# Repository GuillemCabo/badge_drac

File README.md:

# badge_drac
Current schematic has some issues discovered after the first run.
If you are interested to make your own let me know and I will give more priority.

PCB art and FP are fine.

Badges gifted at ORConf 2019 have limited functionality. Only capacitive touch sensors,
buzzer, RGB leds and push buttons were tested.

Code ideas:
Two player reaction time game with touch buttons and LEDs
Closet alarm with ambient light sensor and buzzer.
Coordination minigame, you have to push righ left in function of led color, maybe put some music in the buzzer as well...

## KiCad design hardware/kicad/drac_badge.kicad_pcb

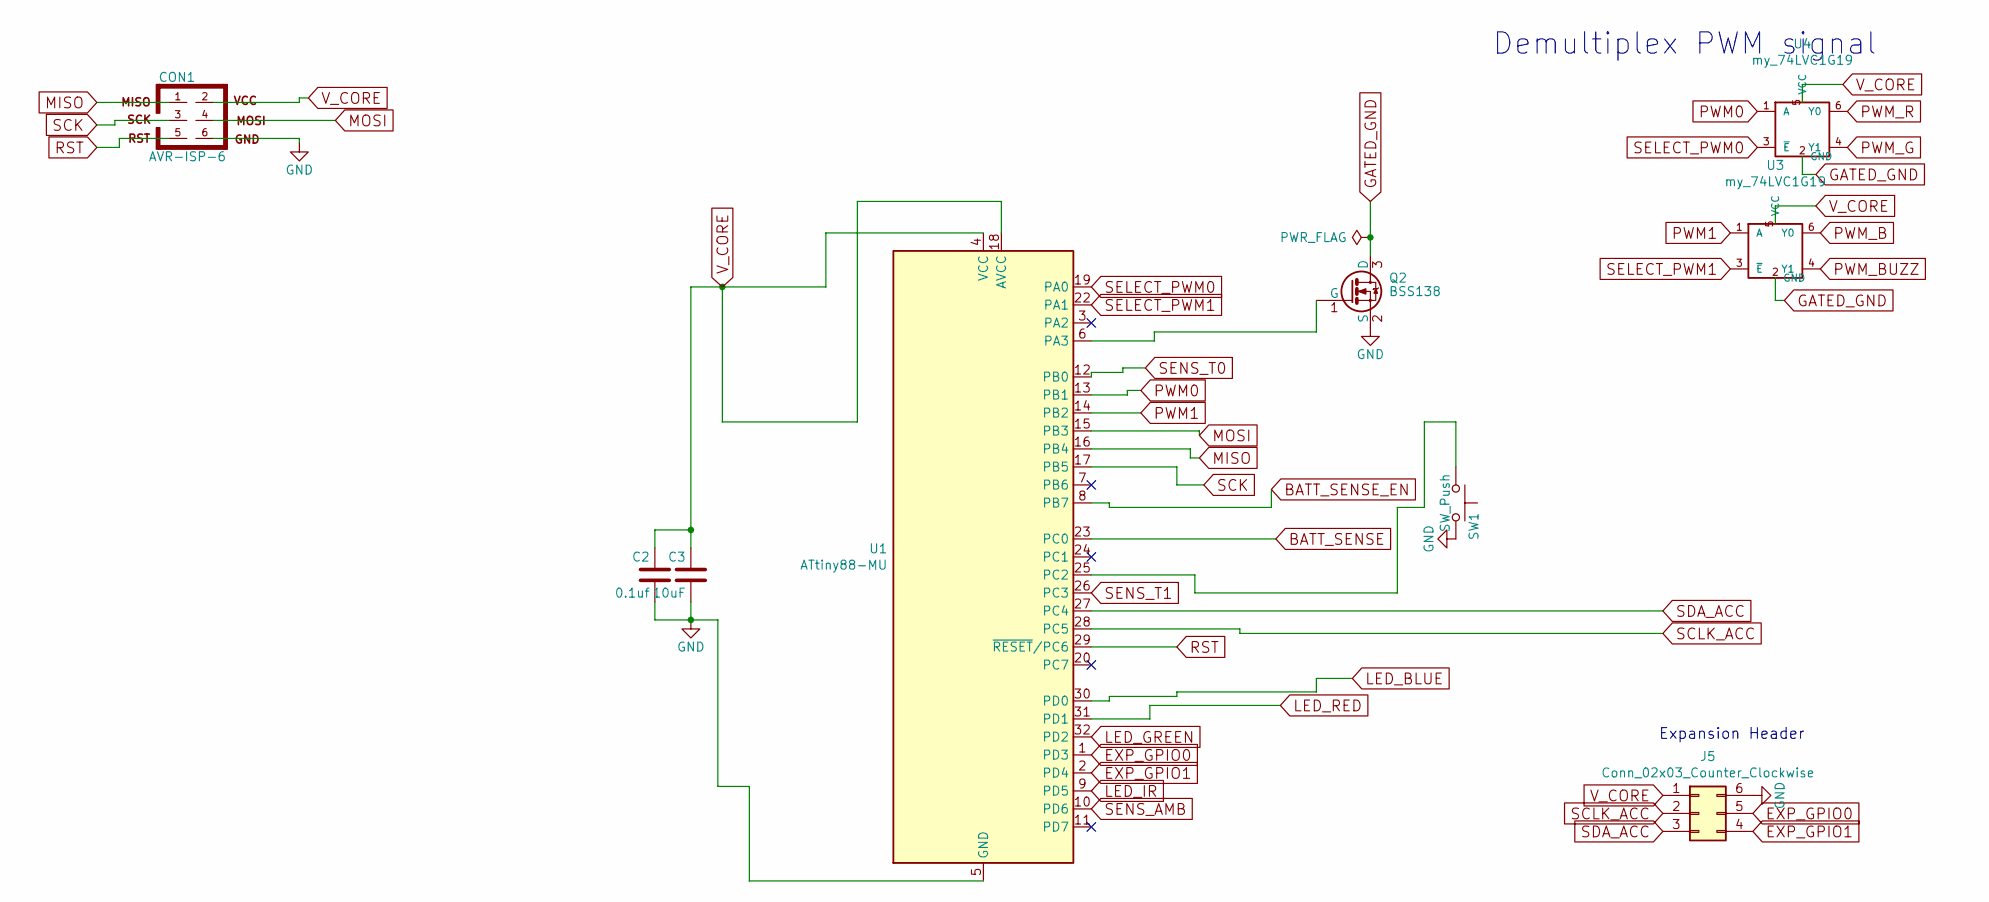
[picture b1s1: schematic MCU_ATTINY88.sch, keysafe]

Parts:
C2: 0.1uf; C_0603_1608Metric; MPN C0603C104J5RACTU; FARNELL # 2409037
C3: 10uF; C_0805_2012Metric; MPN C0805X106K9RACTU; FARNELL # 2776900
CON1: AVR-ISP-6; MERGED_TAGCONNECT_2.54mm; MPN NONE; FARNELL # NONE
J5: Conn_02x03_Counter_Clockwise; PinSocket_2x03_P2.54mm_Vertical_SMD
Q2: BSS138; SOT-23; MPN BSS138PW; FARNELL # 1907611
SW1: SW_Push; SW_Push_1P1T_NO_CK_KSC7xxJ; MPN EVQPUK02K; FARNELL # 2079467
U1: ATtiny88-MU; QFN-32-1EP_5x5mm_P0.5mm_EP3.1x3.1mm; MPN ATTINY88-MU; FARNELL # 1748549
U3, U4: my_74LVC1G19; SOT-363_SC-70-6

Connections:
BATT_SENSE: U1.23 (PC0); also elsewhere on the board
BATT_SENSE_EN: U1.8 (PB7); also elsewhere on the board
EXP_GPIO0: J5.5, U1.1 (PD3)
EXP_GPIO1: J5.4, U1.2 (PD4)
GATED_GND: Q2.3 (D), U3.2 (GND), U4.2 (GND); also elsewhere on the board
GND: C2.2, C3.2, CON1.6, J5.6, Q2.2 (S), SW1.2, U1.5 (GND), U1.21 (GND), U1.33 (GND); also elsewhere on the board
LED_BLUE: U1.30 (PD0); also elsewhere on the board
LED_GREEN: U1.32 (PD2); also elsewhere on the board
LED_IR: U1.9 (PD5); also elsewhere on the board
LED_RED: U1.31 (PD1); also elsewhere on the board
MISO: CON1.1, U1.16 (PB4)
MOSI: CON1.4, U1.15 (PB3)
unnamed: Q2.1 (G), U1.6 (PA3)
unnamed: SW1.1, U1.25 (PC2)
PWM0: U1.13 (PB1), U4.1 (A)
PWM1: U1.14 (PB2), U3.1 (A)
PWM_B: U3.6 (Y0); also elsewhere on the board
PWM_BUZZ: U3.4 (Y1); also elsewhere on the board
PWM_G: U4.4 (Y1); also elsewhere on the board
PWM_R: U4.6 (Y0); also elsewhere on the board
RST: CON1.5, U1.29 (~RESET~/PC6)
SCK: CON1.3, U1.17 (PB5)
SCLK_ACC: J5.2, U1.28 (PC5)
SDA_ACC: J5.3, U1.27 (PC4)
SELECT_PWM0: U1.19 (PA0), U4.3 (~E)
SELECT_PWM1: U1.22 (PA1), U3.3 (~E)
SENS_AMB: U1.10 (PD6); also elsewhere on the board
SENS_T0: U1.12 (PB0); also elsewhere on the board
SENS_T1: U1.26 (PC3); also elsewhere on the board
V_CORE: C2.1, C3.1, CON1.2, J5.1, U1.4 (VCC), U1.18 (AVCC), U3.5 (VCC), U4.5 (VCC); also elsewhere on the board

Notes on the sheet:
Demultiplex PWM signal
Expansion Header

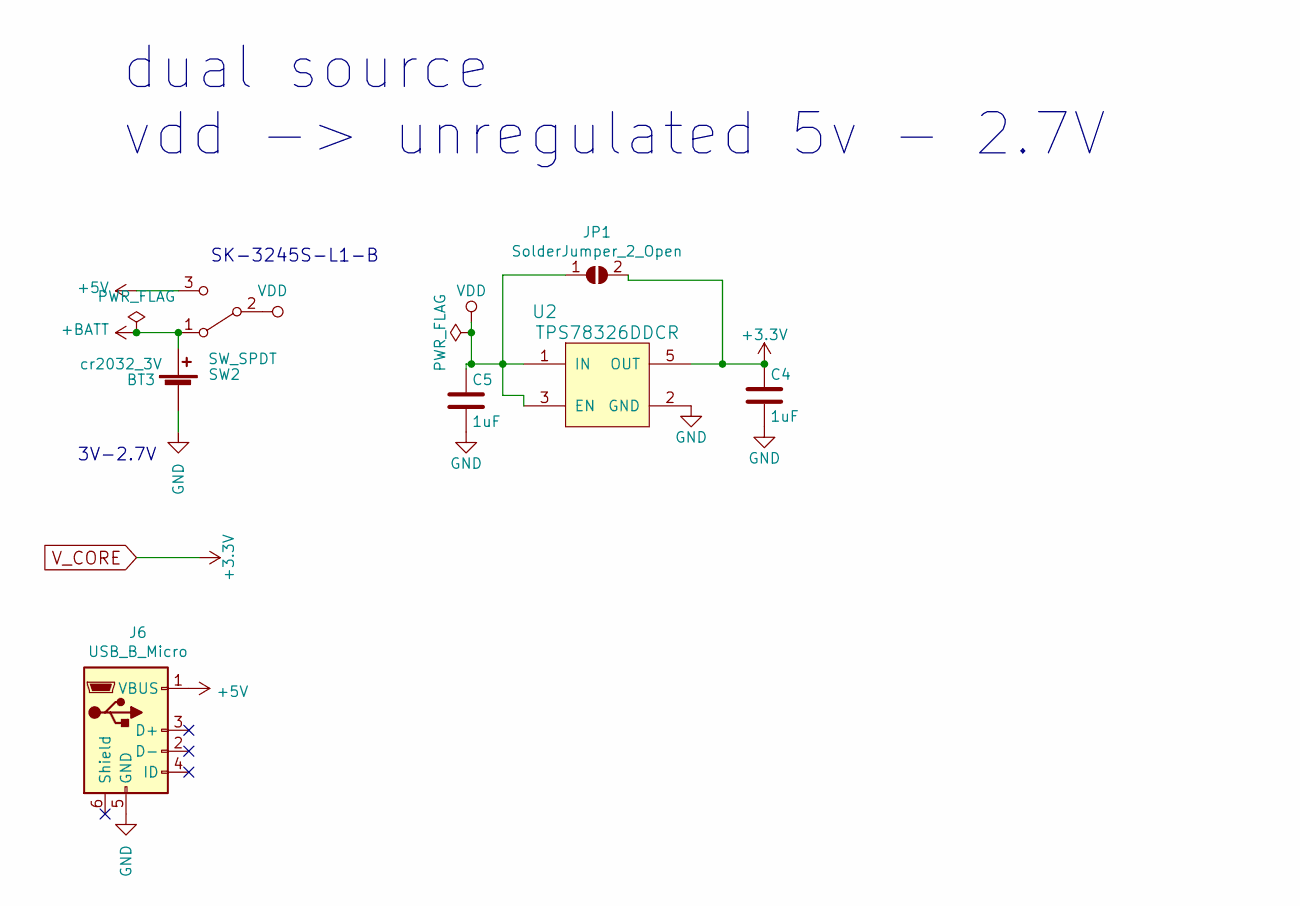
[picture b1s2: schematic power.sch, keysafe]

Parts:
BT3: cr2032_3V; BatteryHolder_Keystone_1060_1x2032; MPN NONE; FARNELL # NONE
C4, C5: 1uF; C_0603_1608Metric; MPN C0603C105K9RACTU; FARNELL # 1865556
J6: USB_B_Micro; microusb_C40945
JP1: SolderJumper_2_Open; SolderJumper-2_P1.3mm_Open_TrianglePad1.0x1.5mm
SW2: SW_SPDT; toogle_sw_K3-2235S-F1
U2: TPS78326DDCR; SOT-23-5; MPN TPS78326DDCR; FARNELL # 2307970

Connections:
+5V: J6.1 (VBUS), SW2.3 (C)
+BATT: BT3.1 (+), SW2.1 (A)
GND: BT3.2 (-), C4.2, C5.2, J6.5 (GND), U2.2 (GND); also elsewhere on the board
VDD: C5.1, JP1.1 (A), SW2.2 (B), U2.1 (IN), U2.3 (EN); also elsewhere on the board
V_CORE: C4.1, JP1.2 (B), U2.5 (OUT); also elsewhere on the board

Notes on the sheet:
3V-2.7V
dual source vdd -> unregulated 5v - 2.7V
SK-3245S-L1-B

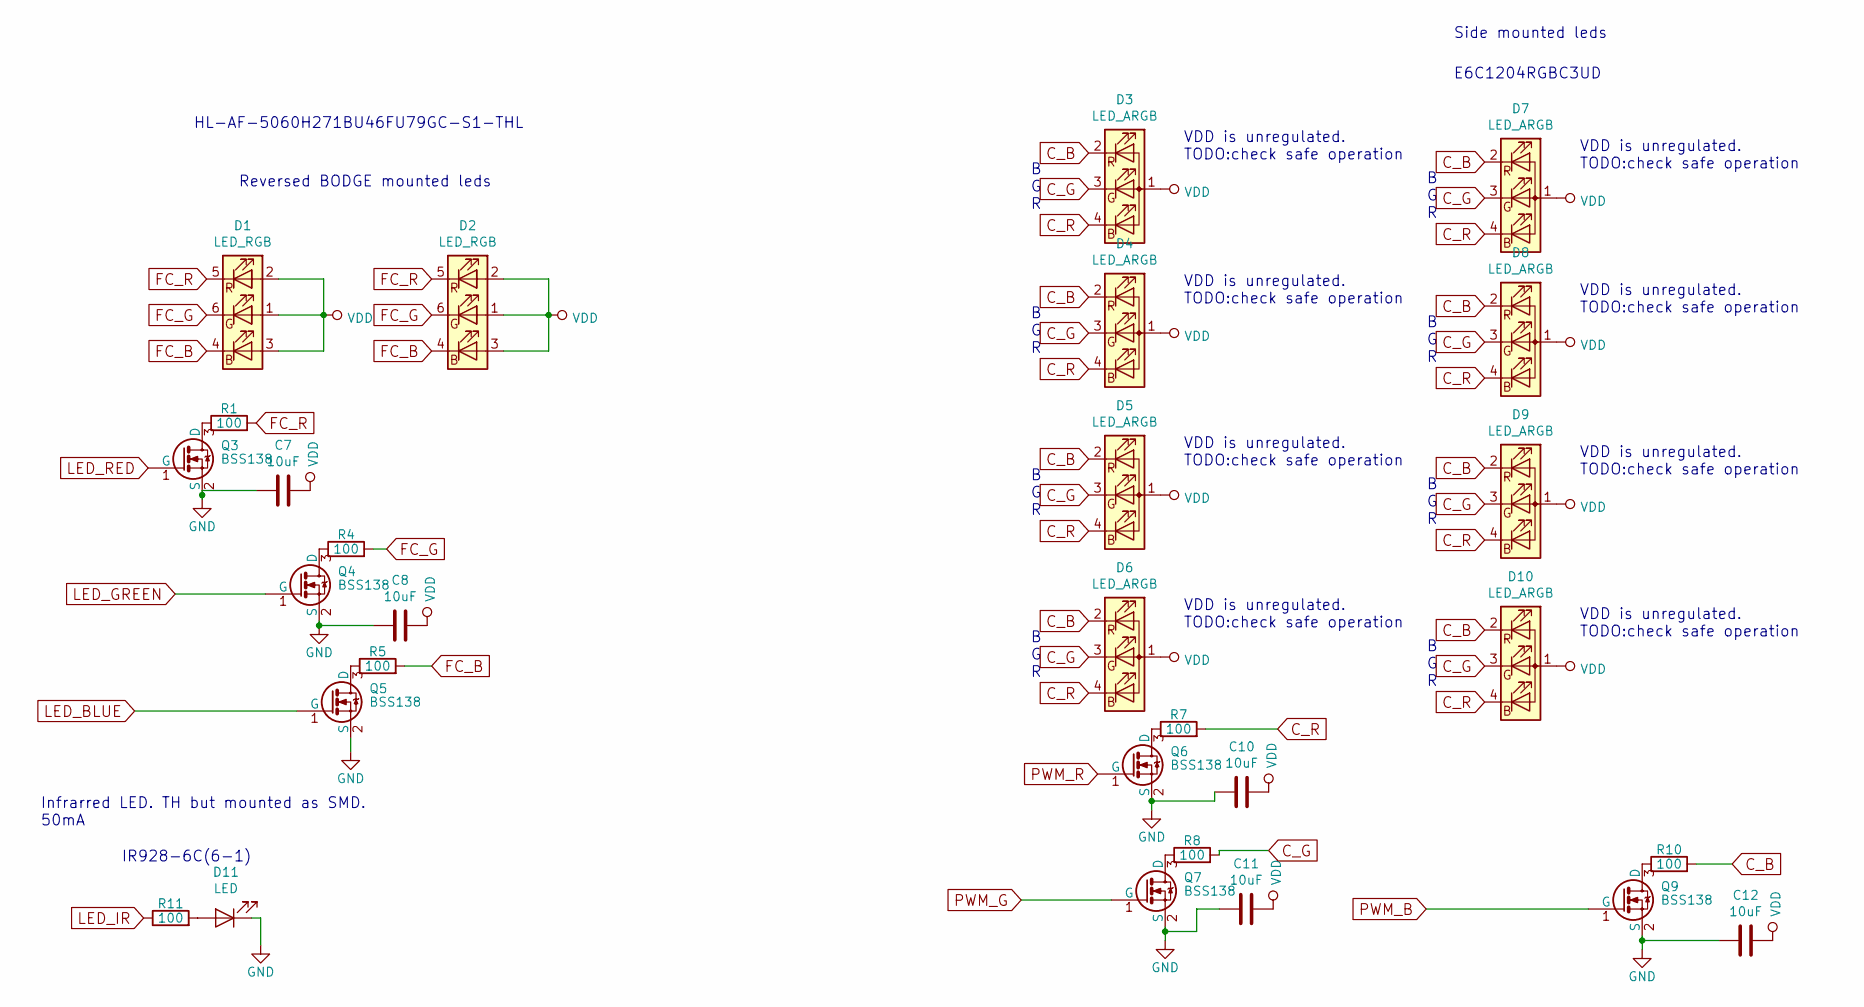
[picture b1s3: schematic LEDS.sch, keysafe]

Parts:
C7, C8, C10, C11, C12: 10uF; C_0805_2012Metric
D1, D2: LED_RGB; LED_RGB_5050-6
D3, D4, D5, D6, D7, D8, D9, D10: LED_ARGB; E6C1204RGBC3
D11: LED; 01x02_wire_solder_smd
Q3, Q4, Q5, Q6, Q7, Q9: BSS138; SOT-23; MPN BSS138PW; FARNELL # 1907611
R1, R4, R5, R7, R8, R10: 100; R_0603_1608Metric; FARNELL # 1469752
R11: 100; R_0805_2012Metric; FARNELL # 1469752

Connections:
C_B: D3.2 (RK), D4.2 (RK), D5.2 (RK), D6.2 (RK), D7.2 (RK), D8.2 (RK), D9.2 (RK), D10.2 (RK), R10.2
C_G: D3.3 (GK), D4.3 (GK), D5.3 (GK), D6.3 (GK), D7.3 (GK), D8.3 (GK), D9.3 (GK), D10.3 (GK), R8.2
C_R: D3.4 (BK), D4.4 (BK), D5.4 (BK), D6.4 (BK), D7.4 (BK), D8.4 (BK), D9.4 (BK), D10.4 (BK), R7.2
FC_B: D1.4 (BK), D2.4 (BK), R5.2
FC_G: D1.6 (GK), D2.6 (GK), R4.2
FC_R: D1.5 (RK), D2.5 (RK), R1.2
GND: C7.2, C8.1, C10.2, C11.2, C12.2, D11.1 (K), Q3.2 (S), Q4.2 (S), Q5.2 (S), Q6.2 (S), Q7.2 (S), Q9.2 (S); also elsewhere on the board
LED_BLUE: Q5.1 (G); also elsewhere on the board
LED_GREEN: Q4.1 (G); also elsewhere on the board
LED_IR: R11.1; also elsewhere on the board
LED_RED: Q3.1 (G); also elsewhere on the board
unnamed: D11.2 (A), R11.2
unnamed: Q3.3 (D), R1.1
unnamed: Q4.3 (D), R4.1
unnamed: Q5.3 (D), R5.1
unnamed: Q6.3 (D), R7.1
unnamed: Q7.3 (D), R8.1
unnamed: Q9.3 (D), R10.1
PWM_B: Q9.1 (G); also elsewhere on the board
PWM_G: Q7.1 (G); also elsewhere on the board
PWM_R: Q6.1 (G); also elsewhere on the board
VDD: C7.1, C8.2, C10.1, C11.1, C12.1, D1.1 (GA), D1.2 (RA), D1.3 (BA), D2.1 (GA), D2.2 (RA), D2.3 (BA), D3.1 (A), D4.1 (A), D5.1 (A), D6.1 (A), D7.1 (A), D8.1 (A), D9.1 (A), D10.1 (A); also elsewhere on the board

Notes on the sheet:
B G R
VDD is unregulated. TODO:check safe operation
E6C1204RGBC3UD
Reversed BODGE mounted leds
Side mounted leds
HL-AF-5060H271BU46FU79GC-S1-THL
IR928-6C(6-1)
Infrarred LED. TH but mounted as SMD. 50mA

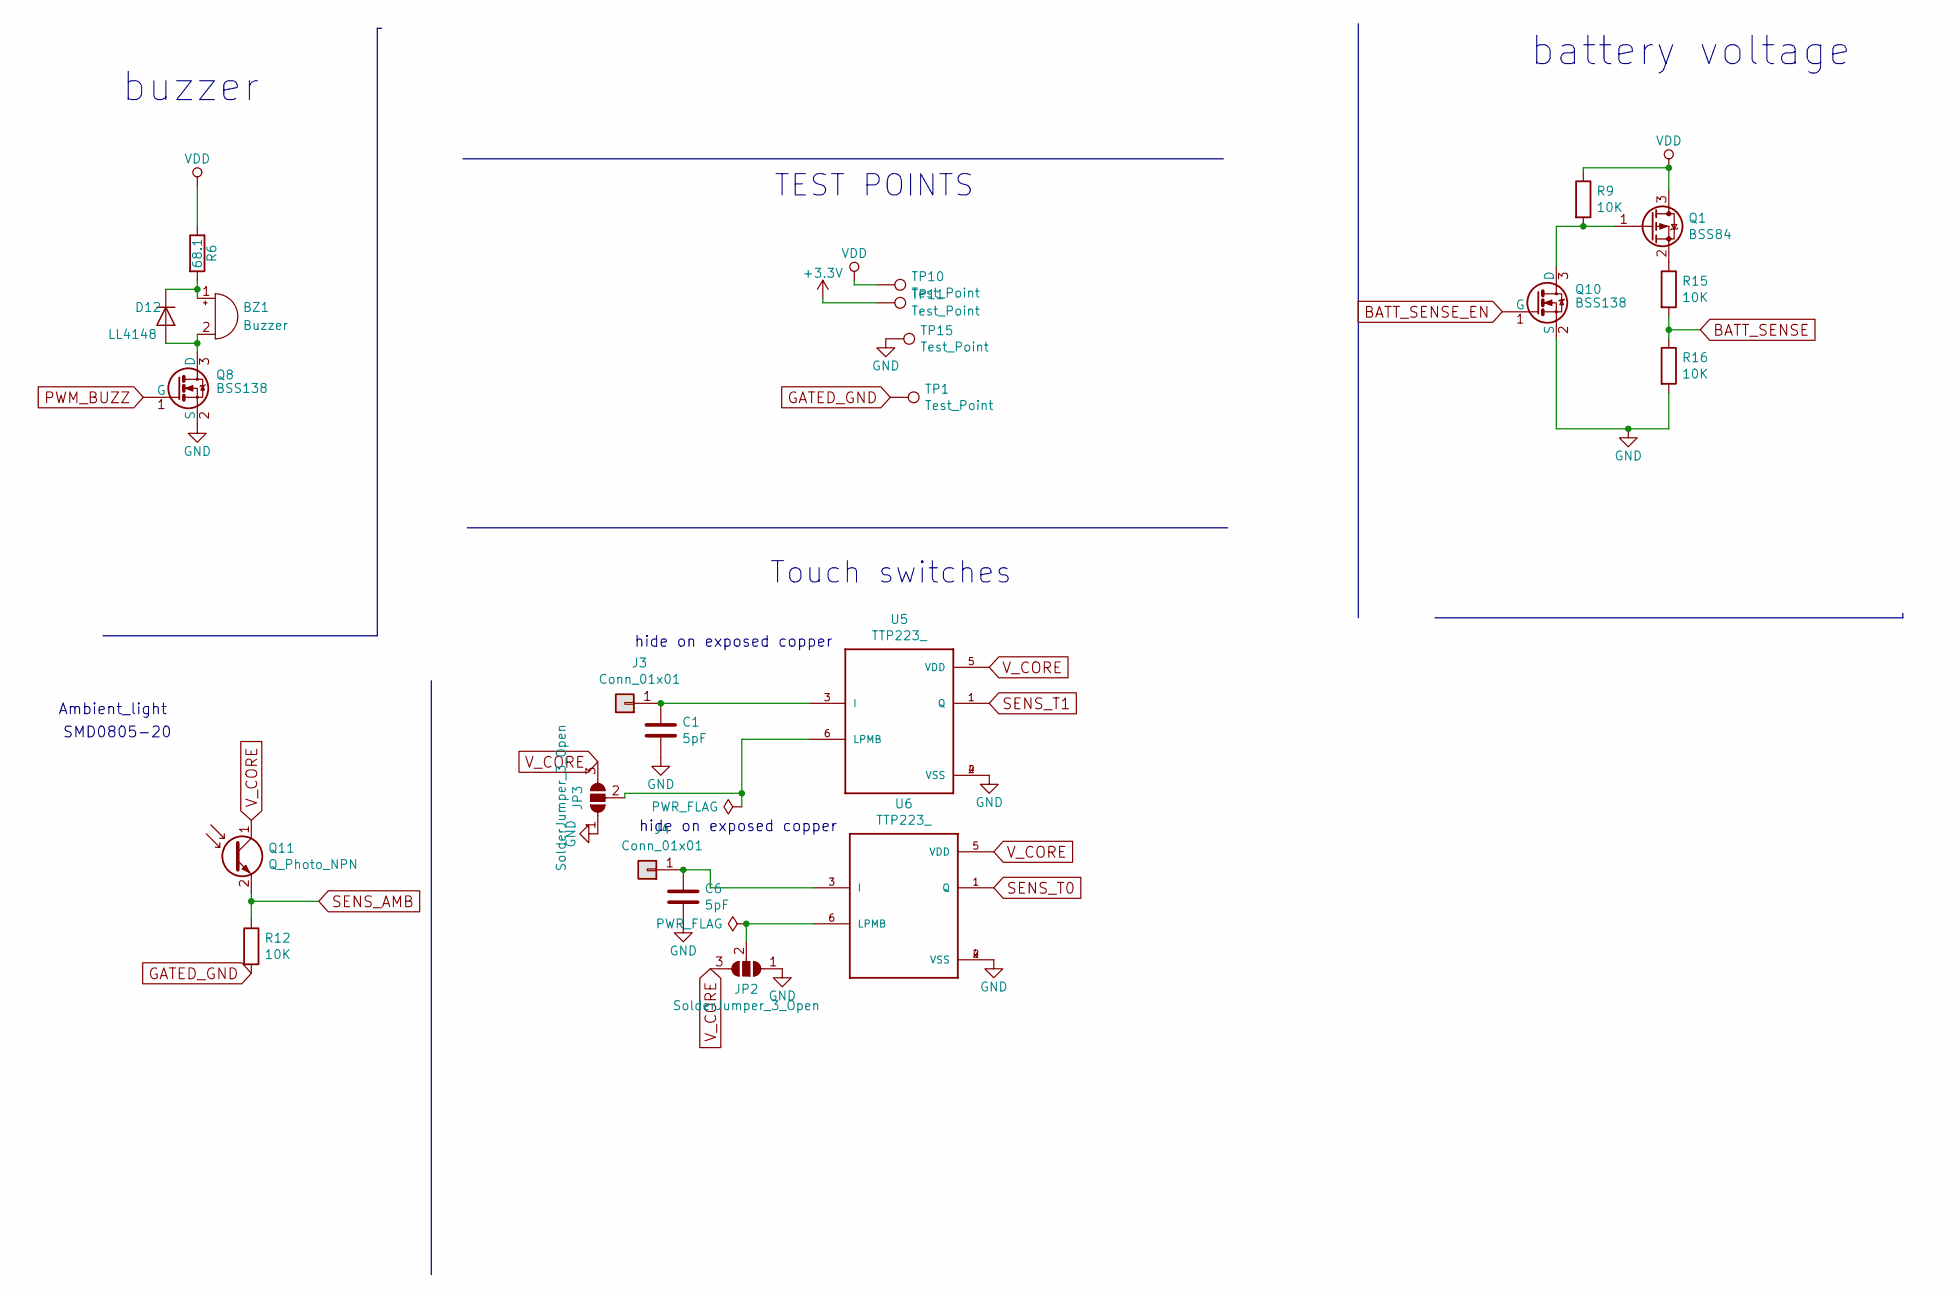
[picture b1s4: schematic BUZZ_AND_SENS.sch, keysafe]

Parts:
BZ1: Buzzer; MLT-9032; MPN NONE; FARNELL # NONE
C1, C6: 5pF; C_0603_1608Metric
D12: LL4148; D_MiniMELF
J3, J4: Conn_01x01; testpoint_small
JP2, JP3: SolderJumper_3_Open; SolderJumper-3_P1.3mm_Bridged2Bar12_Pad1.0x1.5mm_NumberLabe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
Q1: BSS84; SOT-23; MPN BSS84,215; FARNELL # 1510765
Q8, Q10: BSS138; SOT-23; MPN BSS138PW; FARNELL # 1907611
Q11: Q_Photo_NPN; LED_0805_2012Metric_Pad1.15x1.40mm_HandSolder
R6: 68.1; R_1206_3216Metric; MPN MCWR06X68R1FTL; FARNELL # 2694929
R9, R12, R15, R16: 10K; R_0603_1608Metric; MPN CRGH0603F10K; FARNELL # 2332016
TP1, TP15: Test_Point; TestPoint_Pad_2.5x2.5mm; MPN NONE; FARNELL # NONE
TP10, TP11: Test_Point; TestPoint_Pad_D2.5mm; MPN NONE; FARNELL # NONE
U5, U6: TTP223_; SOT95P285X126-6N

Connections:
BATT_SENSE: R15.2, R16.1; also elsewhere on the board
BATT_SENSE_EN: Q10.1 (G); also elsewhere on the board
GATED_GND: R12.2, TP1.1; also elsewhere on the board
GND: C1.2, C6.2, JP2.1 (A), JP3.1 (A), Q8.2 (S), Q10.2 (S), R16.2, TP15.1, U5.2 (VSS), U5.4 (VSS), U6.2 (VSS), U6.4 (VSS); also elsewhere on the board
unnamed: BZ1.1 (-), D12.1 (K), R6.2
unnamed: BZ1.2 (+), D12.2 (A), Q8.3 (D)
unnamed: C1.1, J3.1, U5.3 (I)
unnamed: C6.1, J4.1, U6.3 (I)
unnamed: JP2.2 (C), U6.6 (LPMB)
unnamed: JP3.2 (C), U5.6 (LPMB)
unnamed: Q1.1 (G), Q10.3 (D), R9.2
unnamed: Q1.2 (S), R15.1
PWM_BUZZ: Q8.1 (G); also elsewhere on the board
SENS_AMB: Q11.2 (E), R12.1; also elsewhere on the board
SENS_T0: U6.1 (Q); also elsewhere on the board
SENS_T1: U5.1 (Q); also elsewhere on the board
VDD: Q1.3 (D), R6.1, R9.1, TP10.1; also elsewhere on the board
V_CORE: JP2.3 (B), JP3.3 (B), Q11.1 (C), TP11.1, U5.5 (VDD), U6.5 (VDD); also elsewhere on the board

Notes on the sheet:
buzzer
battery voltage
TEST POINTS
Ambient_light
SMD0805-20
hide on exposed copper
Touch switches

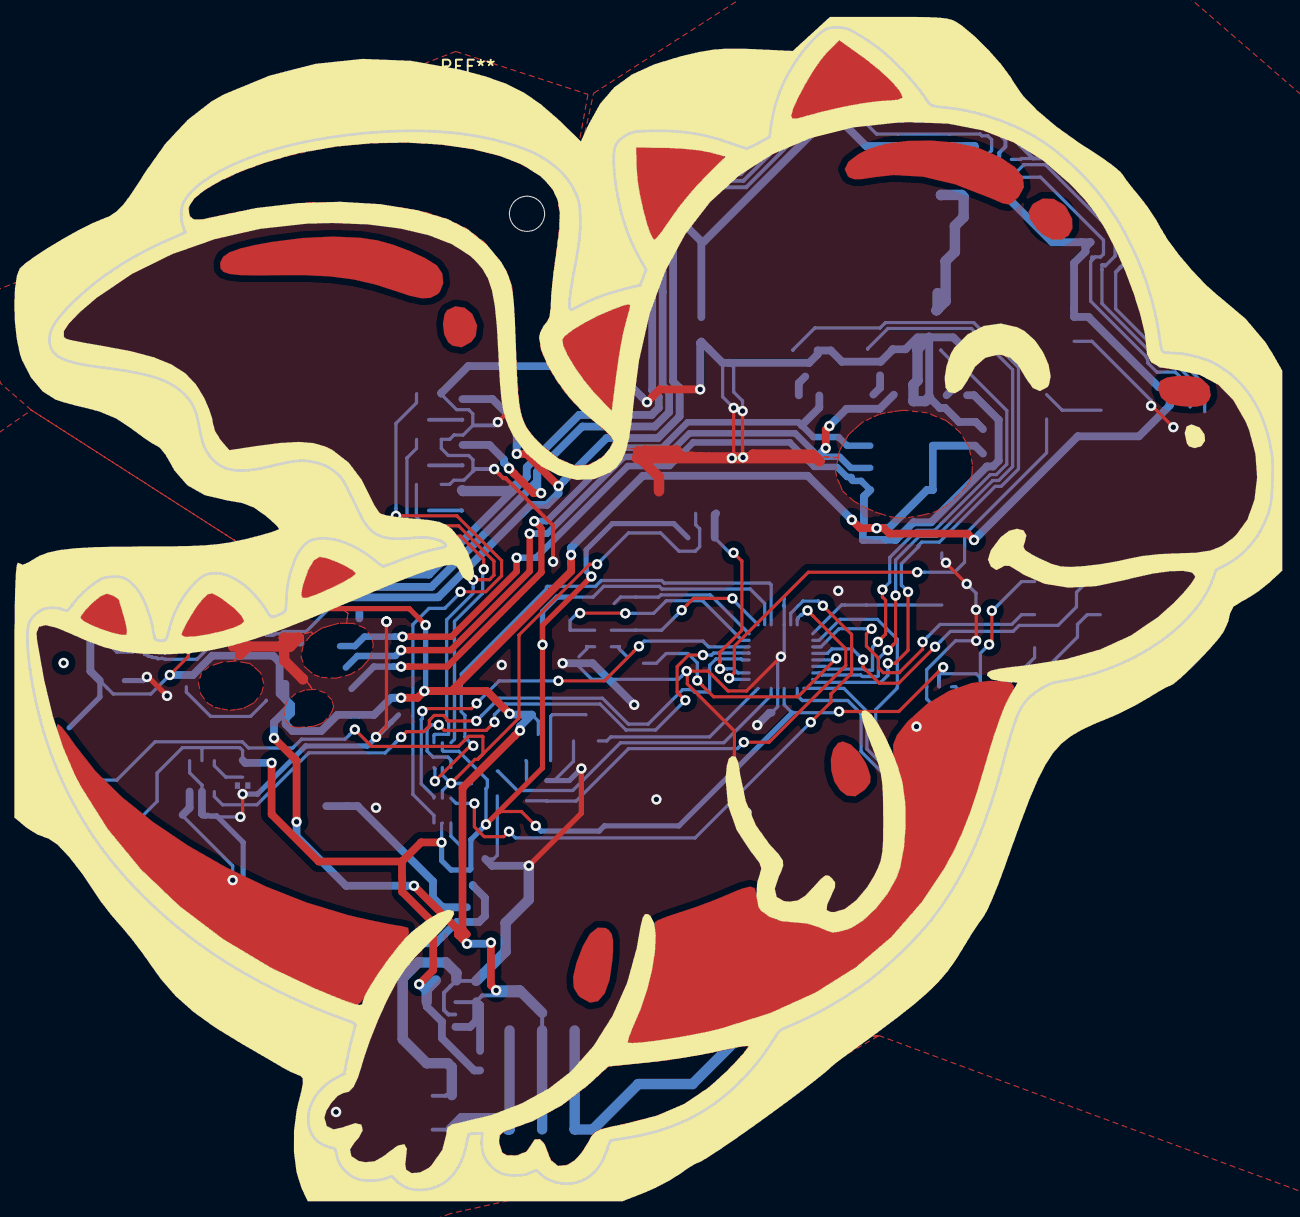
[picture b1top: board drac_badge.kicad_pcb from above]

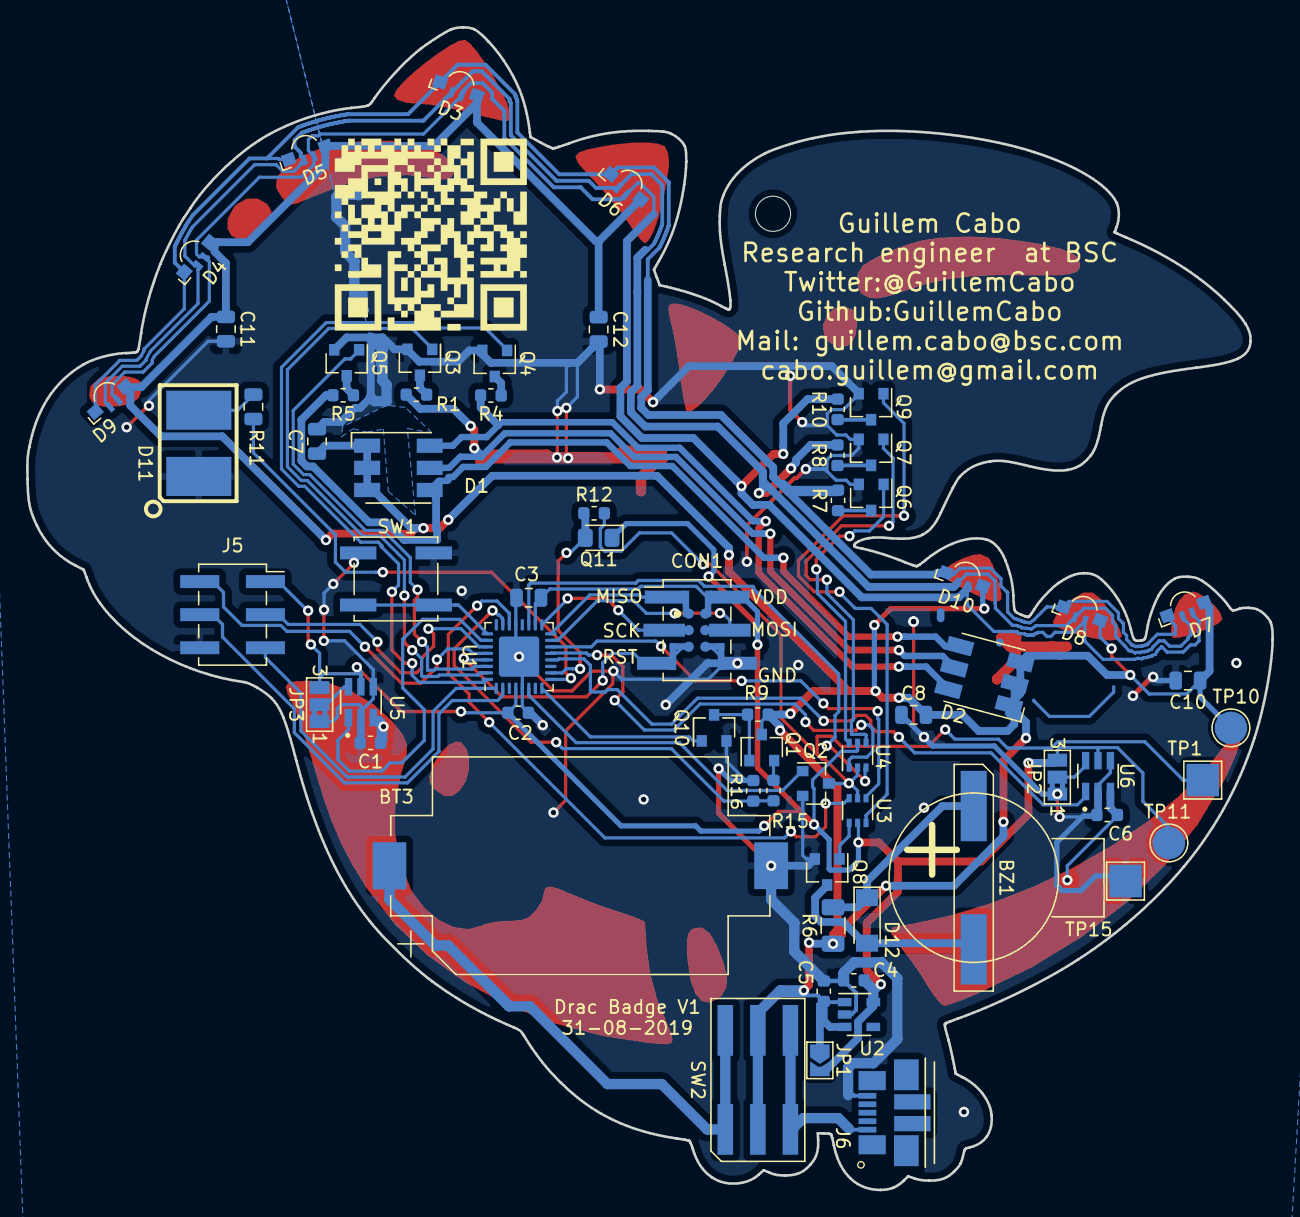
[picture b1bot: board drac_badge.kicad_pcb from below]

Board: 2 copper layers, 95.6 x 89.2 mm, 68 parts (66 on the bottom side), 54 nets.

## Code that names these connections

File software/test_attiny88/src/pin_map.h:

#pragma once
#include <Arduino.h>
#include <config.h>

#ifdef __rev1_patch__   
   //PA0 - 19
   const int PWM_G =23;
   //PA1 - 2
   const int PWM_B =24;
   //PB0 - 12
   const int SENSE_T0=8;
   //PC3 - 26
   const int SENSE_T1=20;
   //PB1 - 13
   const int PWM_R=9;
   //PB2 - 14
   const int PWM_BUZZ=10;
   //PB3 - 15
   const int MY_MOSI=11;
   //PB4 - 16
   const int MY_MISO=12;
   //PB5 - 17
   const int MY_SCK=13;
   //PB7 - 8
   const int BATT_SENSE_EN=15;
   //PC0 - 23
   const int BATT_SENSE=17;
   //PC4 - 27
   const int SDA_ACC=21;
   const int SDA_IR=21;
   //PC5 - 28
   const int SCLK_ACC=22;
   //PC6 - 29
   const int RST=27;
   //PD0 - 30
   const int LED_BLUE=2;
   //PD1 - 31
   const int LED_RED=1;
   //PD2 - 32
   const int LED_GREEN=0;
   //PD3 - 1
   const int EXP_GPIO0=3;
   //PD4 - 2
   const int EXP_GPIO1=4;
   //PD5 - 9
   const int LED_IR=5;
   //PD6 - 10
   const int SENSE_AMB=6;
   //PC2 - 25
   const int SW1=19;
#endif
#ifdef __rev1__   
   //PA0 - 19
   const int SELECT_PWM0 =23;
   //PA1 - 22
   const int SELECT_PWM1 =24;
   //PA3 - 6
   const int ENABLE_GATED_GND=26;
   //PB0 - 12
   const int SENSE_T0=8;
   //PC3 - 26
   const int SENSE_T1=20;
   //PB1 - 13
   const int PWM0=9;
   //PB2 - 14
   const int PWM1=10;
   //PB3 - 15
   const int MY_MOSI=11;
   //PB4 - 16
   const int MY_MISO=12;
   //PB5 - 17
   const int MY_SCK=13;
   //PB7 - 8
   const int BATT_SENSE_EN=15;
   //PC0 - 23
   const int BATT_SENSE=17;
   //PC4 - 27
   const int SDA_ACC=21;
   //PC5 - 28
   const int SCLK_ACC=22;
   //PC6 - 29
   const int RST=27;
   //PD0 - 30
   const int LED_BLUE=2;
   //PD1 - 31
   const int LED_RED=1;
   //PD2 - 32
   const int LED_GREEN=0;
   //PD3 - 1
   const int EXP_GPIO0=3;
   //PD4 - 2
   const int EXP_GPIO1=4;
   //PD5 - 9
   const int LED_IR=5;
   //PD6 - 10
   const int SENSE_AMB=6;
   //PC2 - 25
   const int SW1=19;
#endif

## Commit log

2019-09-19 Quick sample program
2019-09-20 ugly kicad project
2019-09-21 added pin map
2019-09-22 pin map for badge rev1 with jumper wires and example code
    Blink all LEDs, Buzzer tone, ambient light read
